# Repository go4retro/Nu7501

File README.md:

# 7501/8501 to 6502 Adapter Schematic and Printed Circuit Board
This PCB will allow a 65(c)02 CPU to emulate a CSG/MOS 7501/8501 CPU.

## Theory
The 6502 address, data, and r/w lines are fed through the CPLD so they cna be optionally tri-stated, and the on-board PIO port lines 0-6 are emulated.

## Test
This circuit was sucessfully tested on a Commodore C16 with a SD2IEC floppy emulator.
Some pictures of the circuit installed and running:

## License
Copyright (C) 2018  Jim Brain, RETRO Innovations

These files are free designs; you can redistribute them and/or modify
them under the terms of the Creative Commons Attribution-ShareAlike 
4.0 International License.

You should have received a copy of the license along with this
work. If not, see <http://creativecommons.org/licenses/by-sa/4.0/>.

These files are distributed in the hope that they will be useful,
but WITHOUT ANY WARRANTY; without even the implied warranty of
MERCHANTABILITY or FITNESS FOR A PARTICULAR PURPOSE.  See the
license for more details.

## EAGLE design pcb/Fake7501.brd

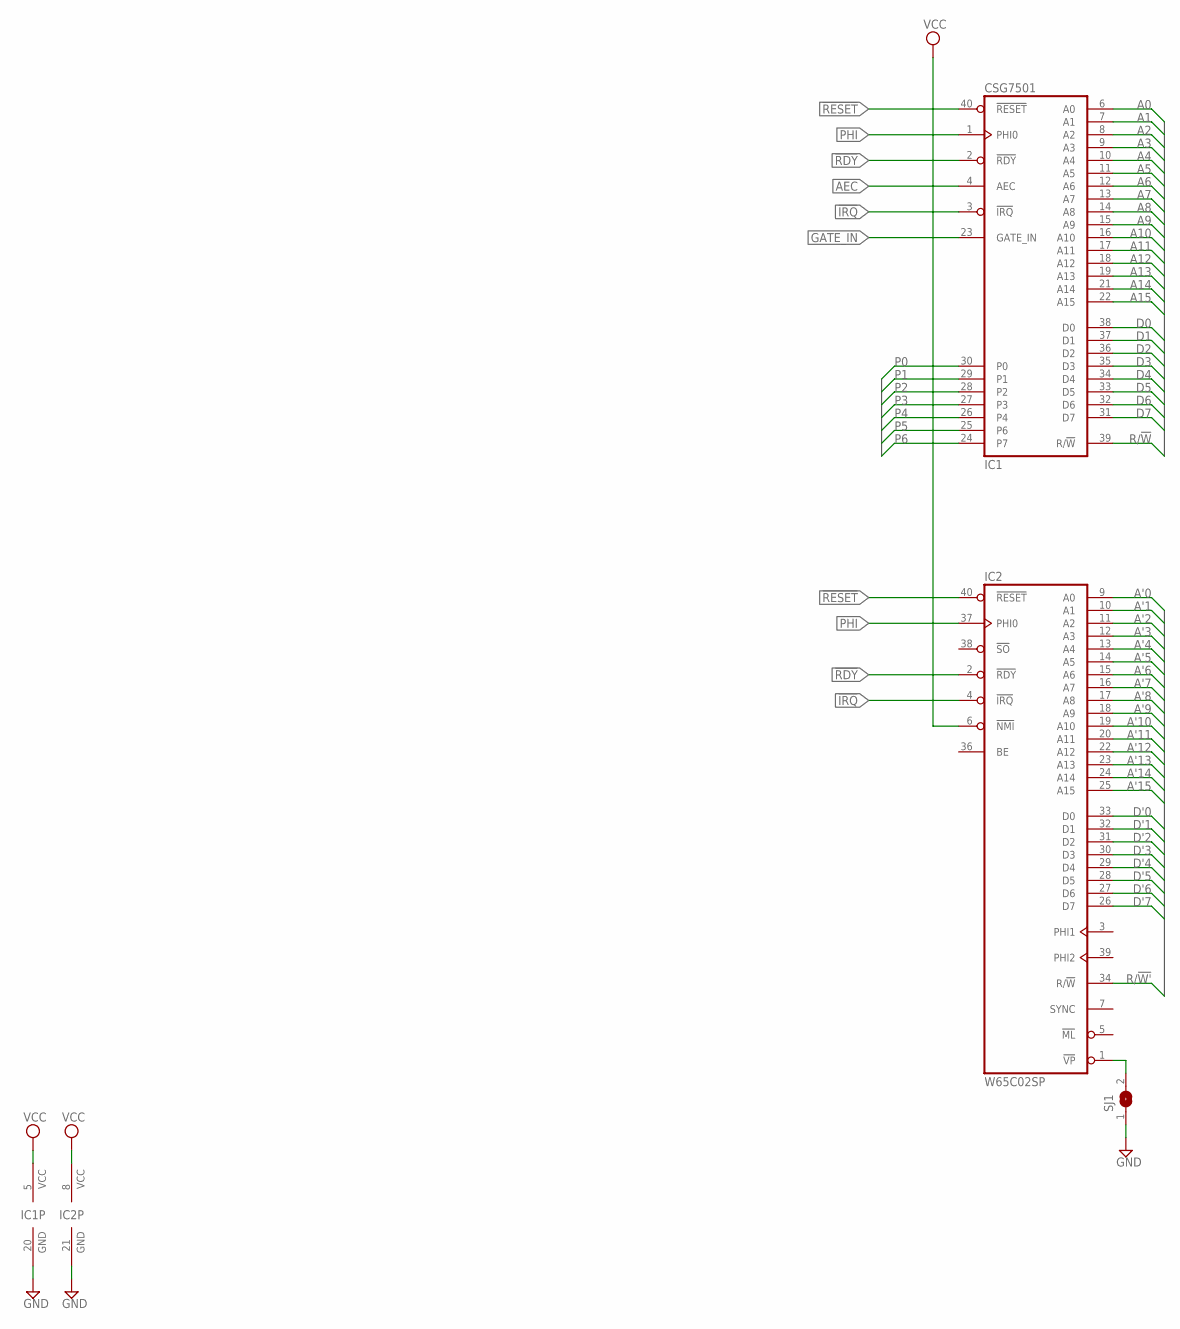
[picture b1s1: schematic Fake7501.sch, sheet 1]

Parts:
IC1: CSG7501; DIL40-ROUNDPAD
IC2: W65C02SP; DIL40-ROUNDPAD
SJ1: SJ

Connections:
!IRQ: IC1.3 (!IRQ), IC2.4 (!IRQ); also elsewhere on the board
!RDY: IC1.2 (!RDY), IC2.2 (!RDY); also elsewhere on the board
!RESET: IC1.40 (!RESET), IC2.40 (!RESET); also elsewhere on the board
A0: IC1.6 (A0); also elsewhere on the board
A1: IC1.7 (A1); also elsewhere on the board
A2: IC1.8 (A2); also elsewhere on the board
A3: IC1.9 (A3); also elsewhere on the board
A4: IC1.10 (A4); also elsewhere on the board
A5: IC1.11 (A5); also elsewhere on the board
A6: IC1.12 (A6); also elsewhere on the board
A7: IC1.13 (A7); also elsewhere on the board
A8: IC1.14 (A8); also elsewhere on the board
A9: IC1.15 (A9); also elsewhere on the board
A10: IC1.16 (A10); also elsewhere on the board
A11: IC1.17 (A11); also elsewhere on the board
A12: IC1.18 (A12); also elsewhere on the board
A13: IC1.19 (A13); also elsewhere on the board
A14: IC1.21 (A14); also elsewhere on the board
A15: IC1.22 (A15); also elsewhere on the board
A'0: IC2.9 (A0); also elsewhere on the board
A'1: IC2.10 (A1); also elsewhere on the board
A'2: IC2.11 (A2); also elsewhere on the board
A'3: IC2.12 (A3); also elsewhere on the board
A'4: IC2.13 (A4); also elsewhere on the board
A'5: IC2.14 (A5); also elsewhere on the board
A'6: IC2.15 (A6); also elsewhere on the board
A'7: IC2.16 (A7); also elsewhere on the board
A'8: IC2.17 (A8); also elsewhere on the board
A'9: IC2.18 (A9); also elsewhere on the board
A'10: IC2.19 (A10); also elsewhere on the board
A'11: IC2.20 (A11); also elsewhere on the board
A'12: IC2.22 (A12); also elsewhere on the board
A'13: IC2.23 (A13); also elsewhere on the board
A'14: IC2.24 (A14); also elsewhere on the board
A'15: IC2.25 (A15); also elsewhere on the board
AEC: IC1.4 (AEC); also elsewhere on the board
D0: IC1.38 (D0); also elsewhere on the board
D1: IC1.37 (D1); also elsewhere on the board
D2: IC1.36 (D2); also elsewhere on the board
D3: IC1.35 (D3); also elsewhere on the board
D4: IC1.34 (D4); also elsewhere on the board
D5: IC1.33 (D5); also elsewhere on the board
D6: IC1.32 (D6); also elsewhere on the board
D7: IC1.31 (D7); also elsewhere on the board
D'0: IC2.33 (D0); also elsewhere on the board
D'1: IC2.32 (D1); also elsewhere on the board
D'2: IC2.31 (D2); also elsewhere on the board
D'3: IC2.30 (D3); also elsewhere on the board
D'4: IC2.29 (D4); also elsewhere on the board
D'5: IC2.28 (D5); also elsewhere on the board
D'6: IC2.27 (D6); also elsewhere on the board
D'7: IC2.26 (D7); also elsewhere on the board
GATE_IN: IC1.23 (GATE_IN); also elsewhere on the board
GND: IC1.20 (GND), IC2.21 (GND), SJ1.1; also elsewhere on the board
unnamed: IC2.1 (!VP), SJ1.2
P0: IC1.30 (P0); also elsewhere on the board
P1: IC1.29 (P1); also elsewhere on the board
P2: IC1.28 (P2); also elsewhere on the board
P3: IC1.27 (P3); also elsewhere on the board
P4: IC1.26 (P4); also elsewhere on the board
P5: IC1.25 (P6); also elsewhere on the board
P6: IC1.24 (P7); also elsewhere on the board
PHI: IC1.1 (PHI0), IC2.37 (PHI0); also elsewhere on the board
R/!W: IC1.39 (R/!W); also elsewhere on the board
R/!W': IC2.34 (R/!W); also elsewhere on the board
VCC: IC1.5 (VCC), IC2.6 (!NMI), IC2.8 (VCC); also elsewhere on the board

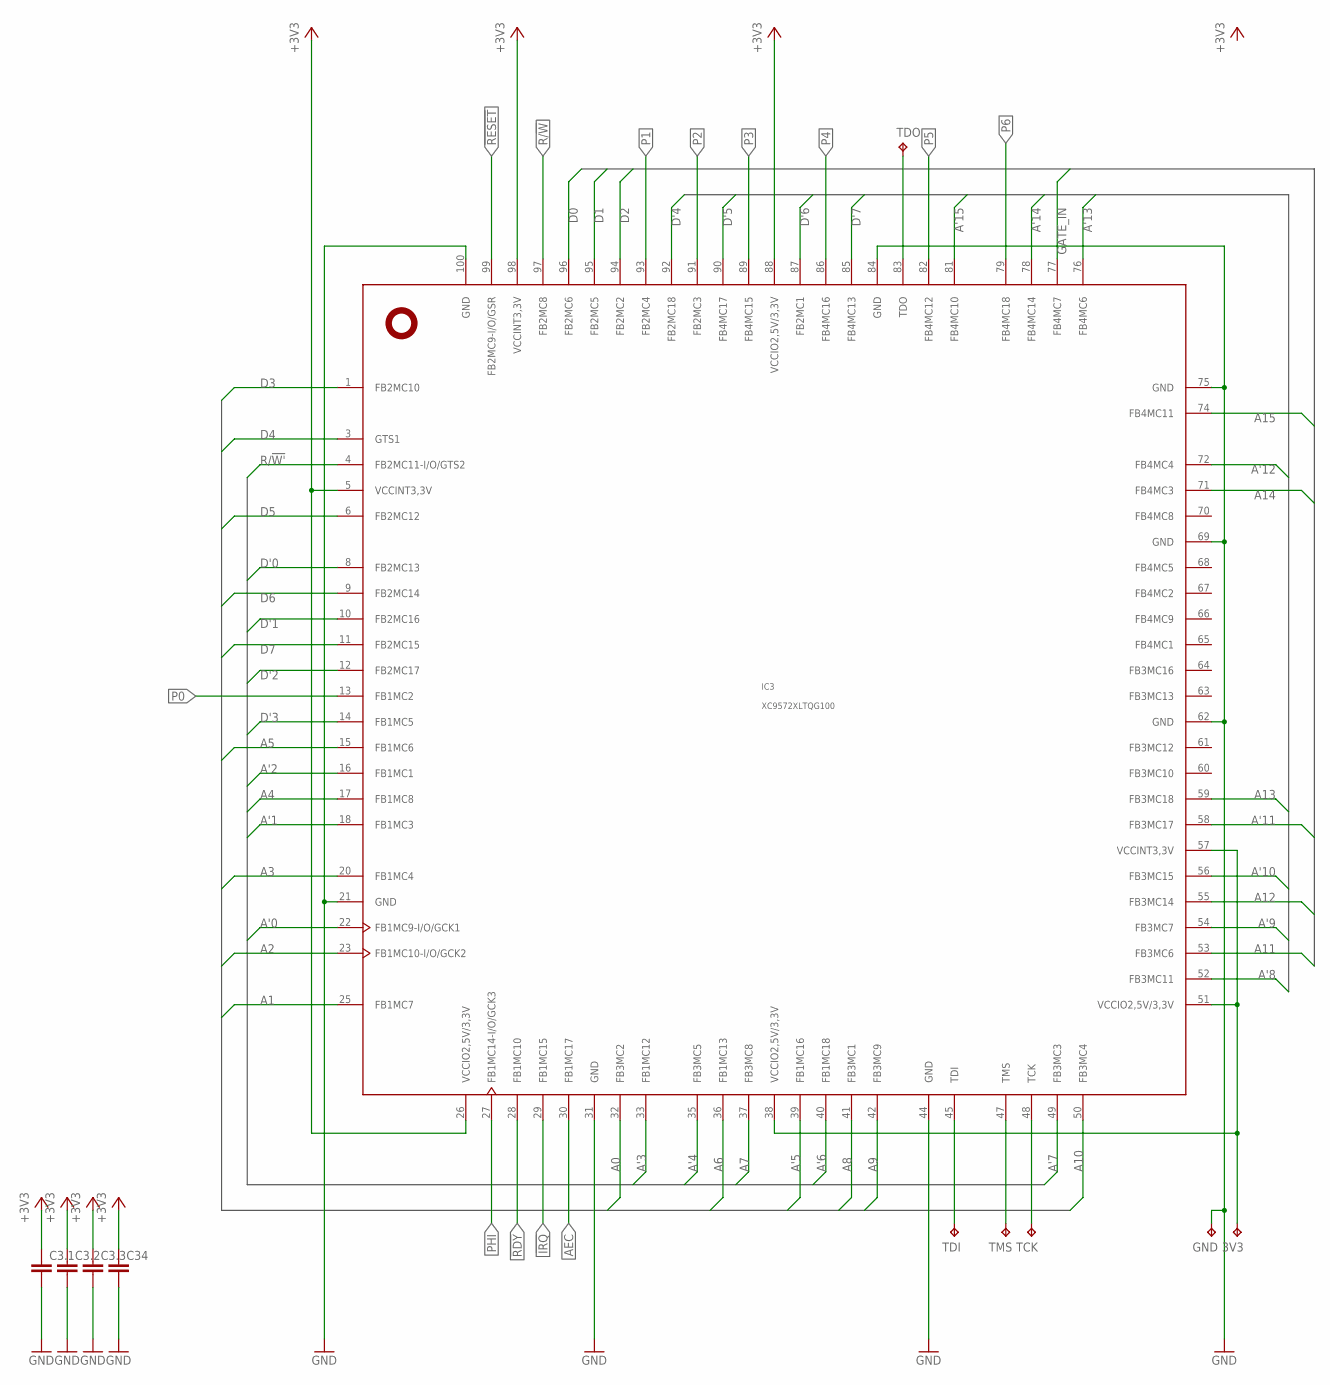
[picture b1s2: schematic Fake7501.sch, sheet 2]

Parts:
3V3: TPTP10SQ; TP10SQ
C3.1, C3.2, C3.3, C34: C-EUC0402; C0402
GND: TPTP10SQ; TP10SQ
IC3: XC9572XLTQG100; TQFP100
TCK: TPTP10SQ; TP10SQ
TDI: TPTP10SQ; TP10SQ
TDO: TPTP10SQ; TP10SQ
TMS: TPTP10SQ; TP10SQ

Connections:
!IRQ: IC3.29 (FB1MC15); also elsewhere on the board
!RDY: IC3.28 (FB1MC10); also elsewhere on the board
!RESET: IC3.99 (FB2MC9-I/O/GSR); also elsewhere on the board
+3V3: 3V3.TP, C3.1.1, C3.2.1, C3.3.1, C34.1, IC3.5 (VCCINT3,3V), IC3.26 (VCCIO2,5V/3,3V), IC3.38 (VCCIO2,5V/3,3V), IC3.51 (VCCIO2,5V/3,3V), IC3.57 (VCCINT3,3V), IC3.88 (VCCIO2,5V/3,3V), IC3.98 (VCCINT3,3V); also elsewhere on the board
A0: IC3.32 (FB3MC2); also elsewhere on the board
A1: IC3.25 (FB1MC7); also elsewhere on the board
A2: IC3.23 (FB1MC10-I/O/GCK2); also elsewhere on the board
A3: IC3.20 (FB1MC4); also elsewhere on the board
A4: IC3.17 (FB1MC8); also elsewhere on the board
A5: IC3.15 (FB1MC6); also elsewhere on the board
A6: IC3.35 (FB3MC5); also elsewhere on the board
A7: IC3.37 (FB3MC8); also elsewhere on the board
A8: IC3.40 (FB1MC18); also elsewhere on the board
A9: IC3.42 (FB3MC9); also elsewhere on the board
A10: IC3.50 (FB3MC4); also elsewhere on the board
A11: IC3.53 (FB3MC6); also elsewhere on the board
A12: IC3.55 (FB3MC14); also elsewhere on the board
A13: IC3.58 (FB3MC17); also elsewhere on the board
A14: IC3.71 (FB4MC3); also elsewhere on the board
A15: IC3.74 (FB4MC11); also elsewhere on the board
A'0: IC3.22 (FB1MC9-I/O/GCK1); also elsewhere on the board
A'1: IC3.18 (FB1MC3); also elsewhere on the board
A'2: IC3.16 (FB1MC1); also elsewhere on the board
A'3: IC3.33 (FB1MC12); also elsewhere on the board
A'4: IC3.36 (FB1MC13); also elsewhere on the board
A'5: IC3.39 (FB1MC16); also elsewhere on the board
A'6: IC3.41 (FB3MC1); also elsewhere on the board
A'7: IC3.49 (FB3MC3); also elsewhere on the board
A'8: IC3.52 (FB3MC11); also elsewhere on the board
A'9: IC3.54 (FB3MC7); also elsewhere on the board
A'10: IC3.56 (FB3MC15); also elsewhere on the board
A'11: IC3.59 (FB3MC18); also elsewhere on the board
A'12: IC3.72 (FB4MC4); also elsewhere on the board
A'13: IC3.76 (FB4MC6); also elsewhere on the board
A'14: IC3.78 (FB4MC14); also elsewhere on the board
A'15: IC3.81 (FB4MC10); also elsewhere on the board
AEC: IC3.30 (FB1MC17); also elsewhere on the board
D0: IC3.96 (FB2MC6); also elsewhere on the board
D1: IC3.95 (FB2MC5); also elsewhere on the board
D2: IC3.94 (FB2MC2); also elsewhere on the board
D3: IC3.1 (FB2MC10); also elsewhere on the board
D4: IC3.3 (GTS1); also elsewhere on the board
D5: IC3.6 (FB2MC12); also elsewhere on the board
D6: IC3.9 (FB2MC14); also elsewhere on the board
D7: IC3.11 (FB2MC15); also elsewhere on the board
D'0: IC3.8 (FB2MC13); also elsewhere on the board
D'1: IC3.10 (FB2MC16); also elsewhere on the board
D'2: IC3.12 (FB2MC17); also elsewhere on the board
D'3: IC3.14 (FB1MC5); also elsewhere on the board
D'4: IC3.92 (FB2MC18); also elsewhere on the board
D'5: IC3.90 (FB4MC17); also elsewhere on the board
D'6: IC3.87 (FB2MC1); also elsewhere on the board
D'7: IC3.85 (FB4MC13); also elsewhere on the board
GATE_IN: IC3.77 (FB4MC7); also elsewhere on the board
GND: C3.1.2, C3.2.2, C3.3.2, C34.2, GND.TP, IC3.21 (GND), IC3.31 (GND), IC3.44 (GND), IC3.62 (GND), IC3.69 (GND), IC3.75 (GND), IC3.84 (GND), IC3.100 (GND); also elsewhere on the board
unnamed: IC3.48 (TCK), TCK.TP
unnamed: IC3.47 (TMS), TMS.TP
unnamed: IC3.45 (TDI), TDI.TP
unnamed: IC3.83 (TDO), TDO.TP
P0: IC3.13 (FB1MC2); also elsewhere on the board
P1: IC3.93 (FB2MC4); also elsewhere on the board
P2: IC3.91 (FB2MC3); also elsewhere on the board
P3: IC3.89 (FB4MC15); also elsewhere on the board
P4: IC3.86 (FB4MC16); also elsewhere on the board
P5: IC3.82 (FB4MC12); also elsewhere on the board
P6: IC3.79 (FB4MC18); also elsewhere on the board
PHI: IC3.27 (FB1MC14-I/O/GCK3); also elsewhere on the board
R/!W: IC3.97 (FB2MC8); also elsewhere on the board
R/!W': IC3.4 (FB2MC11-I/O/GTS2); also elsewhere on the board

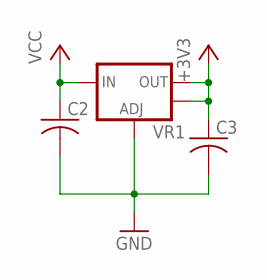
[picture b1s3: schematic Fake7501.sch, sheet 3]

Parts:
C2, C3: C-USC0805; C0805
VR1: V_REG_LM1117SOT223; SOT223

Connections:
+3V3: C3.1, VR1.2 (OUT), VR1.4 (OUT); also elsewhere on the board
GND: C2.2, C3.2, VR1.1 (ADJ); also elsewhere on the board
VCC: C2.1, VR1.3 (IN); also elsewhere on the board

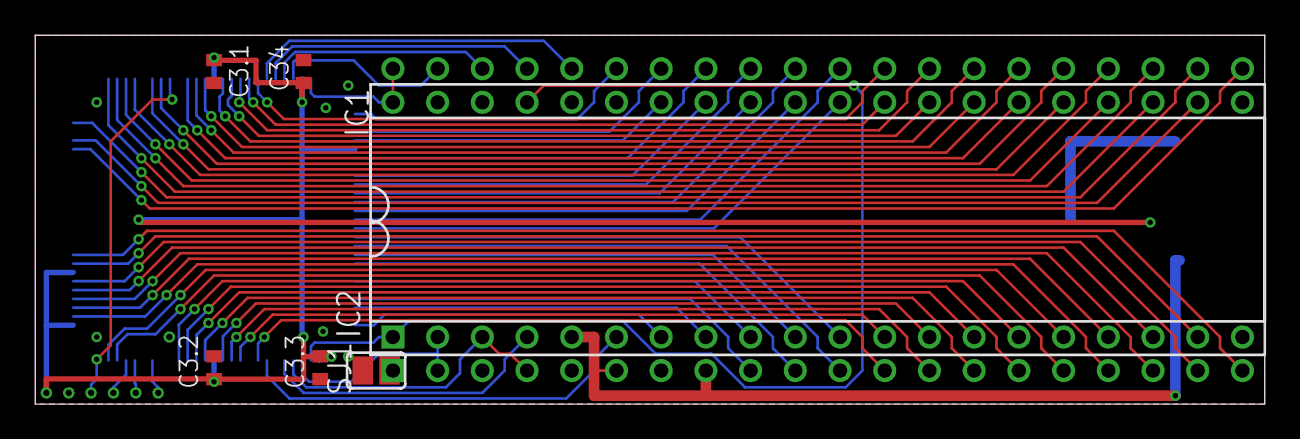
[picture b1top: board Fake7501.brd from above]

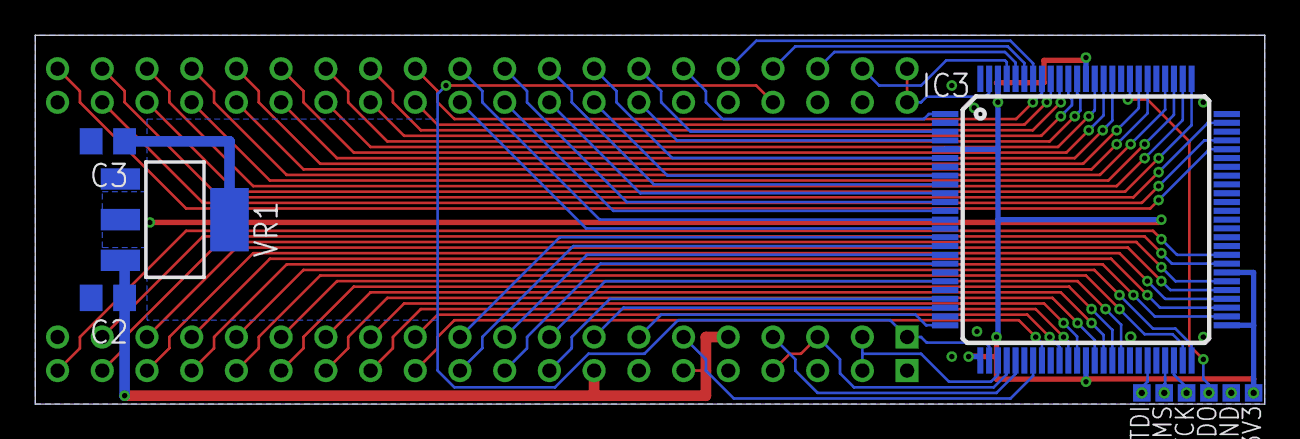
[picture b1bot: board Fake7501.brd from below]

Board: 2 copper layers, 69.8 x 21.0 mm, 17 parts (10 on the bottom side), 71 nets.

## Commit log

2018-06-17 Added initial Verilog HDL
2018-06-17 Fixed logic issue on PIO/DDR writes
2018-06-17 Forgot AEC signal in data line logic
2018-06-19 Updated PCB to fix 7501 footprint errors Added GATE_IN functionality in hdl Added support for 65C02S
2021-10-01 Started to re-work. First version booting C16
2021-10-04 Implemented PIO
2021-10-04 Final version, tested and work well on C16
2021-10-15 Added images
2021-10-28 Works with -10 CPLD
2021-10-28 New way to handle GATE_IN, no more high RAM errors!
2021-12-21 Reset R/W latch

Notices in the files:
parts and their libraries:
SparkFun: Licensing: CC v3.0 Share-Alike You are welcome to use this library for commercial purposes.
